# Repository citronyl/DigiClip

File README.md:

# DigiClip
Electronics project to design wearable PCB hairclips

# LOADING AUDIO
Download audio files and store in seal-loader folder. In terminal run
```bash
ffmpeg -i {filename}.wav -ac 1 -ar 13021 -af highpass=f=400 -f u8 {filename}.raw
```

Set up loader script (only once)
```bash
chmod +x load_all.sh 
```
Plug in clip via UPDI. In terminal run:
```bash
python pack_barks.py {bark1}.raw {bark2}.raw
./load_all.sh
```

## License
This PCB design is open-source hardware licensed under the **CERN Open Hardware Licence Version 2 - Strongly Reciprocal (CERN-OHL-S v2)**. 

You are free to use, study, modify, and distribute these files and manufacture physical hardware based on them, provided that any derivative works or modifications are also shared under the exact same CERN-OHL-S v2 license terms.

For the full legal text, see the [LICENSE](LICENSE) file.

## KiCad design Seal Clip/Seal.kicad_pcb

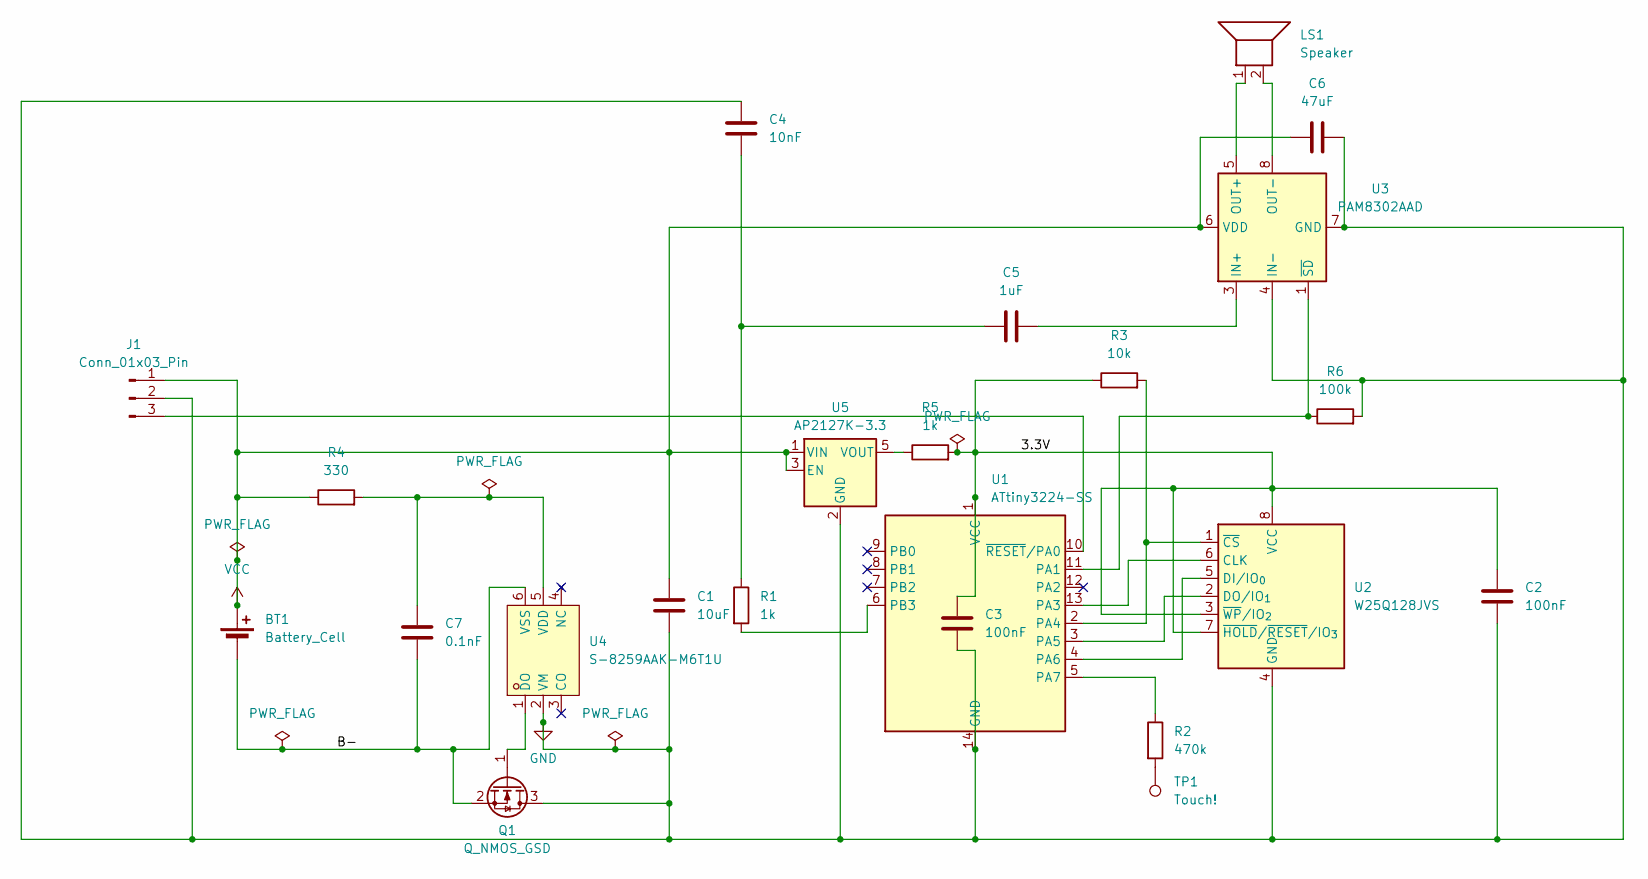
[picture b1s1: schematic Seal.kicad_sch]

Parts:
BT1: Battery_Cell; BatteryClip_Keystone_501
C1: 10uF; C_0805_2012Metric_Pad1.18x1.45mm_HandSolder
C2, C3: 100nF; C_0805_2012Metric_Pad1.18x1.45mm_HandSolder
C4: 10nF; C_0805_2012Metric_Pad1.18x1.45mm_HandSolder
C5: 1uF; C_0805_2012Metric_Pad1.18x1.45mm_HandSolder
C6: 47uF; C_1210_3225Metric_Pad1.33x2.70mm_HandSolder
C7: 0.1nF; C_0805_2012Metric_Pad1.18x1.45mm_HandSolder
J1: Conn_01x03_Pin; PinHeader_1x03_P2.54mm_Vertical
LS1: Speaker; SPKR_CVS-1508
Q1: Q_NMOS_GSD; SuperSOT-3
R1, R5: 1k; R_0805_2012Metric_Pad1.20x1.40mm_HandSolder
R2: 470k; R_0805_2012Metric_Pad1.20x1.40mm_HandSolder
R3: 10k; R_0805_2012Metric_Pad1.20x1.40mm_HandSolder
R4: 330; R_0805_2012Metric_Pad1.20x1.40mm_HandSolder
R6: 100k; R_0805_2012Metric_Pad1.20x1.40mm_HandSolder
TP1: Touch!; TestPoint_Pad_4.0x4.0mm
U1: ATtiny3224-SS; SOIC-14_3.9x8.7mm_P1.27mm
U2: W25Q128JVS; SOIC-8_5.3x5.3mm_P1.27mm
U3: PAM8302AAD; MSOP-8_3x3mm_P0.65mm
U4: S-8259AAK-M6T1U; SOT-23-6_L2.9-W1.6-P0.95-LS2.8-TL; MPN S-8259AAK-M6T1U; LCSC Part C6671296
U5: AP2127K-3.3; SOT-23-5

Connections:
/3.3V: C2.1, C3.2, R3.1, R5.2, U1.1 (VCC), U2.3 (~WP/IO_{2}), U2.7 (~HOLD/~RESET/IO_{3}), U2.8 (VCC)
/B-: BT1.2 (-), C7.1, Q1.2 (S), U4.6 (VSS)
GND: C1.2, C2.2, C3.1, C4.1, C6.2, J1.2, Q1.3 (D), R6.2, U1.14 (GND), U2.4 (GND), U3.4 (IN-), U3.7 (GND), U4.2 (VM), U5.2 (GND); also elsewhere on the board
unnamed: C4.2, C5.1, R1.1
unnamed: J1.3, U1.10 (~RESET/PA0)
unnamed: Q1.1 (G), U4.1 (DO)
unnamed: R2.2, TP1.1 (1_1)
unnamed: R6.1, U1.11 (PA1), U3.1 (~SD)
unnamed: U1.13 (PA3), U2.6 (CLK)
unnamed: R3.2, U1.2 (PA4), U2.1 (~CS)
unnamed: U1.3 (PA5), U2.2 (DO/IO_{1})
unnamed: U1.4 (PA6), U2.5 (DI/IO_{0})
unnamed: R2.1, U1.5 (PA7)
unnamed: R1.2, U1.6 (PB3)
unnamed: C5.2, U3.3 (IN+)
unnamed: LS1.1, U3.5 (OUT+)
unnamed: LS1.2, U3.8 (OUT-)
unnamed: C7.2, R4.2, U4.5 (VDD)
unnamed: R5.1, U5.5 (VOUT)
VCC: BT1.1 (+), C1.1, C6.1, J1.1, R4.1, U3.6 (VDD), U5.1 (VIN), U5.3 (EN)

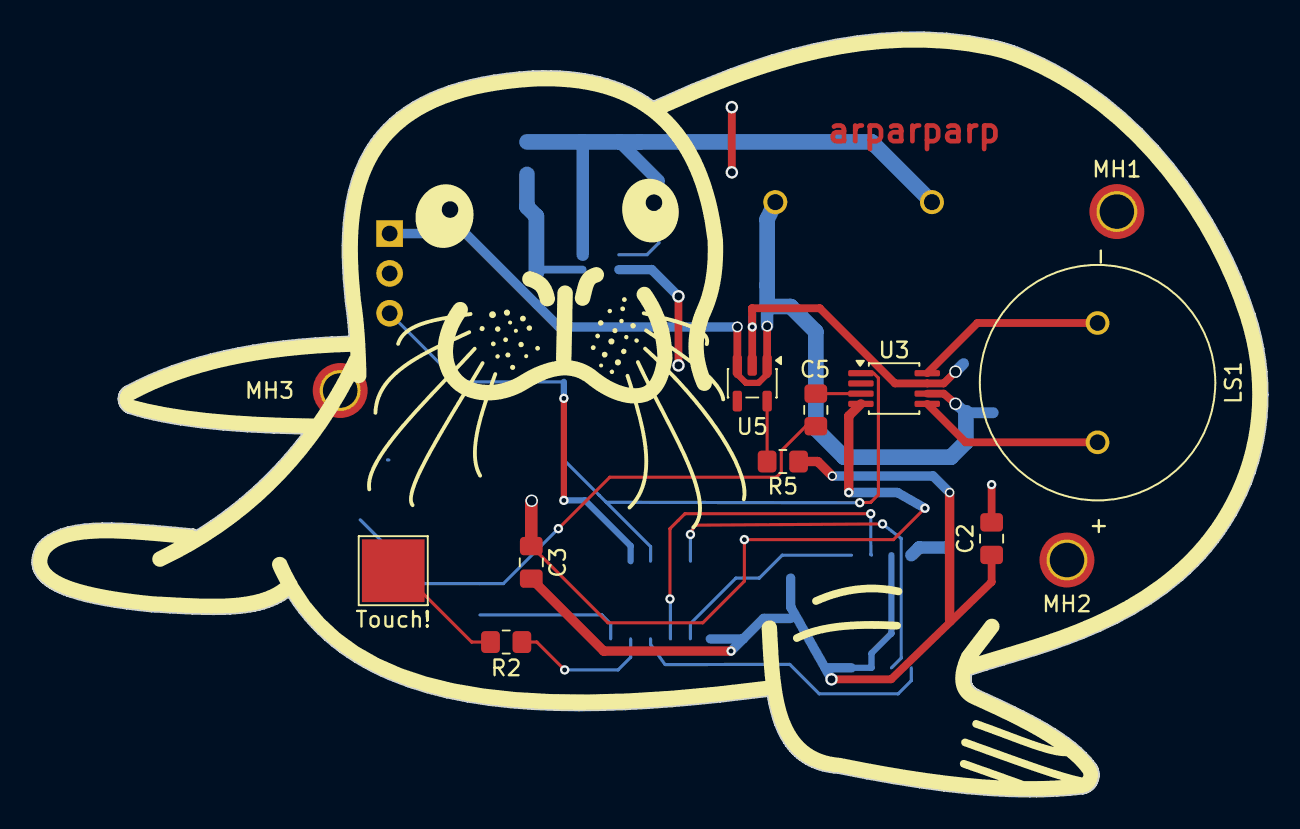
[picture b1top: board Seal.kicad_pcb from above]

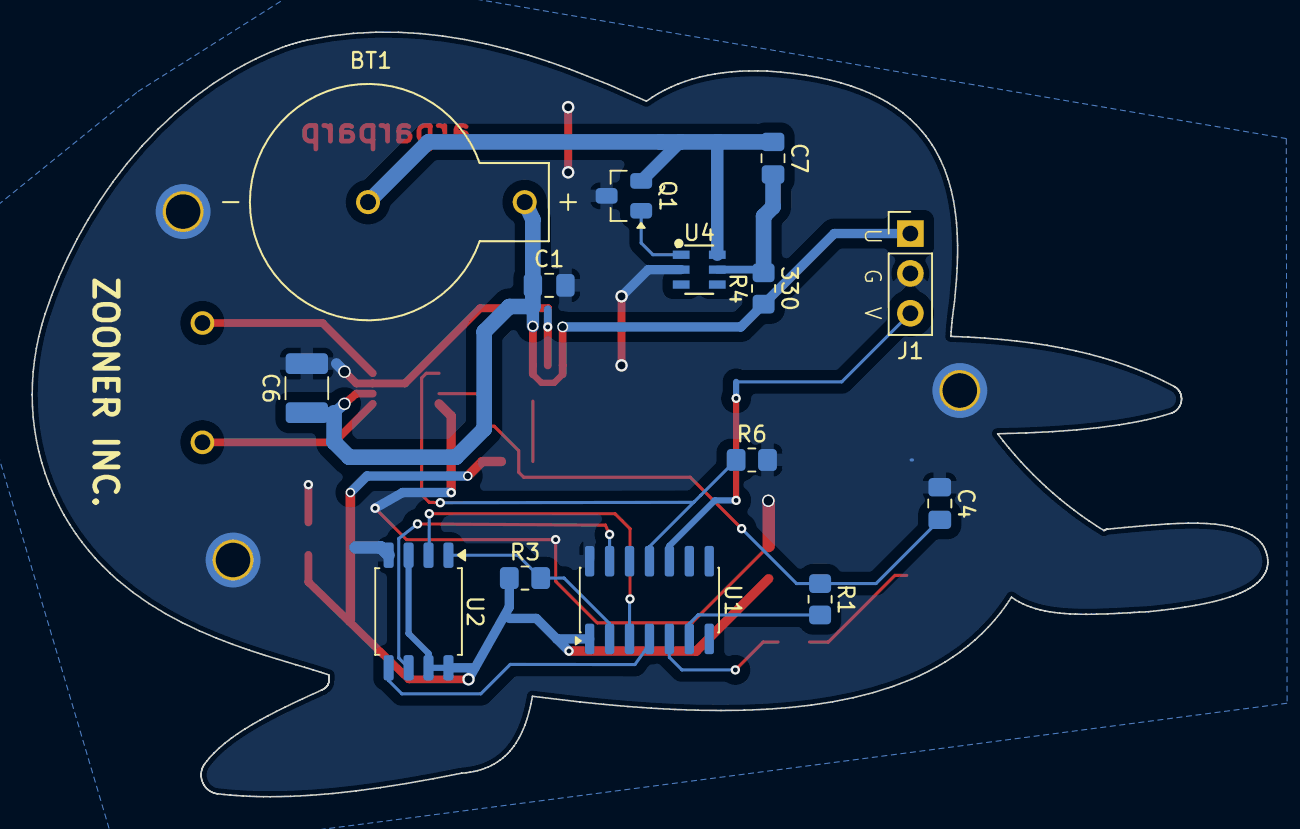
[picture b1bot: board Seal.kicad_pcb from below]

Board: 2 copper layers, 78.7 x 48.7 mm, 26 parts (14 on the bottom side), 20 nets.

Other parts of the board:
MH1, MH2, MH3: MountingHole_2.2mm_M2_ISO7380_Pad_TopBottom

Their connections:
GND: MH1.1, MH2.1, MH3.1; also elsewhere on the board

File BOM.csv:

"Reference","Value","Footprint","Qty"
"BT1","Battery_Cell","Battery:BatteryClip_Keystone_501","1"
"C1","10uF","Capacitor_SMD:C_0805_2012Metric_Pad1.18x1.45mm_HandSolder","1"
"C2","100nF","Capacitor_SMD:C_0805_2012Metric_Pad1.18x1.45mm_HandSolder","1"
"C3","100nF","Capacitor_SMD:C_0805_2012Metric_Pad1.18x1.45mm_HandSolder","1"
"C4","10nF","Capacitor_SMD:C_0805_2012Metric_Pad1.18x1.45mm_HandSolder","1"
"C5","1uF","Capacitor_SMD:C_0805_2012Metric_Pad1.18x1.45mm_HandSolder","1"
"C6","47uF","Capacitor_SMD:C_1210_3225Metric_Pad1.33x2.70mm_HandSolder","1"
"C7","0.1nF","Capacitor_SMD:C_0805_2012Metric_Pad1.18x1.45mm_HandSolder","1"
"J1","Conn_01x03_Pin","Connector_PinHeader_2.54mm:PinHeader_1x03_P2.54mm_Vertical","1"
"LS1","Speaker","Speaker:SPKR_CVS-1508","1"
"Q1","Q_NMOS_DGS","Package_TO_SOT_SMD:SuperSOT-3","1"
"R1","1k","Resistor_SMD:R_0805_2012Metric_Pad1.20x1.40mm_HandSolder","1"
"R2","470k","Resistor_SMD:R_0805_2012Metric_Pad1.20x1.40mm_HandSolder","1"
"R3","10k","Resistor_SMD:R_0805_2012Metric_Pad1.20x1.40mm_HandSolder","1"
"R4","330","Resistor_SMD:R_0805_2012Metric_Pad1.20x1.40mm_HandSolder","1"
"R5","1uF","Resistor_SMD:R_0805_2012Metric_Pad1.20x1.40mm_HandSolder","1"
"R6","100k","Resistor_SMD:R_0805_2012Metric_Pad1.20x1.40mm_HandSolder","1"
"U1","ATtiny3224-SS","Package_SO:SOIC-14_3.9x8.7mm_P1.27mm","1"
"U2","W25Q128JVS","Package_SO:SOIC-8_5.3x5.3mm_P1.27mm","1"
"U3","PAM8302AAD","Package_SO:MSOP-8_3x3mm_P0.65mm","1"
"U4","S-8259AAK-M6T1U","easyeda2kicad:SOT-23-6_L2.9-W1.6-P0.95-LS2.8-TL","1"
"U5","AP2127K-3.3","Package_TO_SOT_SMD:SOT-23-5","1"

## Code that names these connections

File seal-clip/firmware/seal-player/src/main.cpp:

#include <Arduino.h>
#include <avr/sleep.h>
#include <avr/eeprom.h>
#include <util/delay.h>

// 8-bit PWM: PER = 255 -> 10 MHz / 256 = 39,062.5 Hz carrier
// One sample every 5 PWM cycles -> 7,812.5 samples per second
#define PWM_TOP        255
#define PWM_MID        128          // 50% duty = silence
#define CYCLES_PER_SEC 39063UL      // waitOverflows(CYCLES_PER_SEC) = ~1 s
#define CYCLES_SETTLE  3906         // ~0.1 s
#define CYCLES_SAMPLE  5            // 7,812.5 Hz

#define VOLUME        8             // 0..8
#define TOUCH_ON      400
#define TOUCH_OFF     200
#define LOCKOUT_WAKES 8             // 8 x 125 ms = 1 s (RTC, unaffected by the PWM)
#define MAX_CLIPS     32

#define F_CS   PIN4_bm              // PA4
#define F_SCK  PIN3_bm              // PA3
#define F_MOSI PIN6_bm              // PA6
#define F_MISO PIN5_bm              // PA5

uint16_t baseline;
uint8_t  clipCount = 0;
uint32_t clipStart[MAX_CLIPS], clipLen[MAX_CLIPS];
uint16_t rng = 1;

ISR(RTC_PIT_vect) { RTC.PITINTFLAGS = RTC_PI_bm; }

// ---------- timing ----------
void waitOverflows(uint32_t n) {                // one count = one PWM cycle (25.6 µs)
  while (n--) {
    while (!(TCA0.SINGLE.INTFLAGS & TCA_SINGLE_OVF_bm)) {}
    TCA0.SINGLE.INTFLAGS = TCA_SINGLE_OVF_bm;
  }
}

// ---------- flash ----------
void csLow()  { PORTA.OUTCLR = F_CS; }
void csHigh() { PORTA.OUTSET = F_CS; }

uint8_t spi(uint8_t out) {
  uint8_t in = 0;
  for (uint8_t i = 0; i < 8; i++) {
    if (out & 0x80) PORTA.OUTSET = F_MOSI; else PORTA.OUTCLR = F_MOSI;
    out <<= 1;
    PORTA.OUTSET = F_SCK;
    in <<= 1;
    if (PORTA.IN & F_MISO) in |= 1;
    PORTA.OUTCLR = F_SCK;
  }
  return in;
}

void sendAddr(uint32_t a) { spi(a >> 16); spi(a >> 8); spi(a); }

void flashWake() {
  PORTA.PIN5CTRL = PORT_ISC_INTDISABLE_gc;      // MISO input buffer on
  csLow(); spi(0xAB); csHigh();
  _delay_us(10);
}

void flashSleep() {
  csLow(); spi(0xB9); csHigh();                 // deep power-down, ~1 µA
  PORTA.PIN5CTRL = PORT_ISC_INPUT_DISABLE_gc;   // MISO buffer off
}

uint32_t read32() {
  uint32_t v = spi(0);
  v |= (uint32_t)spi(0) << 8;
  v |= (uint32_t)spi(0) << 16;
  v |= (uint32_t)spi(0) << 24;
  return v;
}

void readTable() {
  flashWake();
  csLow(); spi(0x03); sendAddr(0);
  char sig[4];
  for (uint8_t i = 0; i < 4; i++) sig[i] = spi(0);
  uint16_t n = spi(0); n |= (uint16_t)spi(0) << 8;
  if (sig[0] == 'S' && sig[1] == 'E' && sig[2] == 'A' && sig[3] == 'L' && n >= 1 && n <= MAX_CLIPS) {
    clipCount = n;
    for (uint8_t k = 0; k < n; k++) { clipStart[k] = read32(); clipLen[k] = read32(); }
  }
  csHigh();
  flashSleep();
}

// ---------- touch ----------
uint16_t touchOnce() {
  analogRead(PIN_PB1);                          // empty the ADC sample cap
  PORTA.OUTSET = PIN7_bm; PORTA.DIRSET = PIN7_bm;   // charge the pad
  _delay_us(10);
  PORTA.DIRCLR = PIN7_bm;                       // release and measure
  uint16_t v = analogRead(PIN_PA7);
  PORTA.OUTCLR = PIN7_bm; PORTA.DIRSET = PIN7_bm;   // park at 0 V
  return v;
}

uint16_t touchRead(uint8_t n) {
  ADC0.CTRLA |= ADC_ENABLE_bm;
  _delay_us(50);
  uint32_t sum = 0;
  for (uint8_t i = 0; i < n; i++) sum += touchOnce();
  ADC0.CTRLA &= ~ADC_ENABLE_bm;
  return sum / n;
}

// ---------- random pick ----------
uint16_t rnd() {
  rng ^= rng << 7; rng ^= rng >> 9; rng ^= rng << 8;
  return rng;
}

uint8_t pickClip() {
  static uint8_t last = 255;
  if (clipCount == 1) return 0;
  uint8_t k;
  do { k = rnd() % clipCount; } while (k == last);
  last = k;
  return k;
}

// ---------- playback ----------
void playClip(uint8_t k) {
  cli();
  flashWake();
  csLow(); spi(0x03); sendAddr(clipStart[k]);
  digitalWrite(PIN_PA1, HIGH);                  // amp on
  waitOverflows(CYCLES_SETTLE);
  for (uint32_t i = 0; i < clipLen[k]; i++) {
    int16_t v = (int16_t)spi(0) - 128;          // 0..255 -> -128..127
    v = (v * VOLUME) / 8;
    v = PWM_MID + v;                            // full 8 bits, no halving
    if (v < 0)       v = 0;
    if (v > PWM_TOP) v = PWM_TOP;
    TCA0.SINGLE.CMP0BUF = (uint8_t)v;
    waitOverflows(CYCLES_SAMPLE);
  }
  csHigh();
  TCA0.SINGLE.CMP0BUF = PWM_MID;
  waitOverflows(CYCLES_SETTLE);
  digitalWrite(PIN_PA1, LOW);                   // amp off
  flashSleep();
  sei();
}

void sleepOnce() { sei(); sleep_cpu(); }

void setup() {
  cli();
  pinMode(PIN_PA1, OUTPUT); digitalWrite(PIN_PA1, LOW);
  pinMode(PIN_PB1, OUTPUT); digitalWrite(PIN_PB1, LOW);
  PORTB.DIRSET = PIN3_bm;
  PORTA.OUTSET = F_CS;
  PORTA.OUTCLR = F_SCK | F_MOSI;
  PORTA.DIRSET = F_CS | F_SCK | F_MOSI;
  PORTA.DIRCLR = F_MISO;
  PORTA.OUTCLR = PIN7_bm; PORTA.DIRSET = PIN7_bm;

  PORTA.PIN7CTRL = PORT_ISC_INPUT_DISABLE_gc;
  PORTA.PIN2CTRL = PORT_ISC_INPUT_DISABLE_gc;
  PORTB.PIN0CTRL = PORT_ISC_INPUT_DISABLE_gc;
  PORTB.PIN2CTRL = PORT_ISC_INPUT_DISABLE_gc;

  analogReadResolution(12);

  takeOverTCA0();
  PORTMUX.TCAROUTEA |= 0x01;                    // WO0 -> PB3
  TCA0.SINGLE.CTRLB = TCA_SINGLE_WGMODE_SINGLESLOPE_gc | TCA_SINGLE_CMP0EN_bm;
  TCA0.SINGLE.PER  = PWM_TOP;
  TCA0.SINGLE.CMP0 = PWM_MID;
  TCA0.SINGLE.CTRLA = TCA_SINGLE_CLKSEL_DIV1_gc | TCA_SINGLE_ENABLE_bm;

  readTable();

  uint16_t boots = eeprom_read_word((uint16_t*)0) + 1;
  eeprom_update_word((uint16_t*)0, boots);

  waitOverflows(CYCLES_PER_SEC);                // 1 s hands off
  baseline = touchRead(16);
  rng = (boots * 2654435761UL >> 16) ^ baseline;
  if (rng == 0) rng = 1;

  RTC.CLKSEL = RTC_CLKSEL_INT32K_gc;
  while (RTC.PITSTATUS > 0) {}
  RTC.PITINTCTRL = RTC_PI_bm;
  RTC.PITCTRLA = RTC_PERIOD_CYC4096_gc | RTC_PITEN_bm;   // wake every 125 ms

  set_sleep_mode(SLEEP_MODE_PWR_DOWN);
  sleep_enable();
}

void loop() {
  static bool armed = true;

  sleepOnce();
  uint16_t r = touchRead(4);
  rng ^= r;
  if (rng == 0) rng = 1;

  if (!armed) {
    if (r < baseline + TOUCH_OFF) armed = true;
    return;
  }

  if (r > baseline + TOUCH_ON && clipCount > 0) {
    _delay_ms(5); if (touchRead(4) <= baseline + TOUCH_ON) return;
    _delay_ms(5); if (touchRead(4) <= baseline + TOUCH_ON) return;
    playClip(pickClip());
    for (uint8_t i = 0; i < LOCKOUT_WAKES; i++) sleepOnce();
    armed = false;
  } else if (r < baseline + TOUCH_OFF) {
    baseline = (baseline * 15UL + r) / 16;
  }
}
